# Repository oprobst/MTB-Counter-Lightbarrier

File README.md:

# Lichtschranke mit Unterbrechungszähler

Diese Implementierung wurde mit dem Hintergrund erstellt, auf einem Mountain-Bike Trail die Anzahl der Durchfahrten zu messen. Mit kleineren Anpassungen, kann diese Schaltung aber auch für alles Mögliche verwendet werden.

* Ziel ist es, die Unterbrechungen der Lichtschranke zu zählen. Dies wird über den gesamten Lebenszyklus, wie auch auf täglicher Basis gezählt.
* Weitere Anforderung ist ein möglichst geringer Stromverbrauch, um einen Einsatz mit Batterie im Feld zu vereinfachen.

# Bedienungsanleitung

An der rechten oberen Seite der Verteilerdose ist ein Magnetkontakt angebracht. Dieser kann genutzt werden, um das Display zu aktivieren. Sobald ein Magnet an das Gehäuse gehalten wird, aktiviert sich das Display für 5 Minuten. Im Normalbetrieb ist das Display aus, um Strom zu sparen und um zu verhindern, dass Fuchs und Hase daran herum spielen. Ein weiterer Vorteil des Magneten liegt darin, dass eine fehleranfällige Gehäusedurchführung für einen Taster eingespart werden kann.

## Display
Auf dem Display sind mehrere Zahlen abgebildet. Links oben ist die Gesamtzahl der aufgezeichneten Unterbrechungen. Diese Zahl wird mit jeder Durchfahrt um einen Zähler erhöht.

In der unteren Zeile sind die vergangenen Tage dokumentiert. Es wird immer dann eine neue Zählung begonnen, wenn der Helligkeitssensor einen Sonnenaufgang registriert oder wenn das System neu gestartet (oder resettet) wird.
Dabei steht jede Zahl für einen Tag. In dem unten abgebildeten Beispiel sind am heutigen Tag 15 Fahrten, gestern 0 und vorgestern 1 Unterbrechung gemessen worden. Der Speicher lässt nur 253 Zählungen zu, finden mehr Durchfahrten an einem Tag statt, so zeigt das Display 'MAX' an. Dies beeinflusst allerdings nicht die Zählung der gesamten Durchgänge oben links.

Um mehr als die letzten 4 Tage anzuzeigen, schaltet der Zähler mehrere Seiten durch. Dabei wird jede Seite wird für 5 Sekunden angezeigt. Im Beispiel befindet sich der Zähler noch auf Seite 0, visualisiert durch die Angabe 'P0'. Folglich wird in der Zeile unten auf erster Stelle der aktuelle Tag und im Weiteren die vergangenen drei Tage dargestellt.
Würde hier z.B. 'P3' stehen, so rechne man einfach die (Page)3 * 4(Tage) um auf den Tag des ersten Wertes in der Vergangenheit zu kommen. In diesem Fall würde man also die Durchfahrten von vor 12, vor 13, vor 14 und vor 15 Tagen angezeigt bekommen.

Letztlich steht ganz rechts oben eine Zahl mit einer Nachkommastelle. Hierbei handelt es sich um die aktuelle Batteriespannung. Sie muss im Regelfall zwischen 9V und 14V liegen. Liegt sie darunter, lädt die Solarzelle die Batterie nicht mehr. Liegt sie darüber, ist irgendetwas magisches passiert.

Der Kontrast des Displays lässt sich mit einer Stellschraube auf halber Höhe des Zählers einstellen.

## Zähler zurück setzen

Es ist möglich den Zähler auf 0 zurück zu setzen. Dafür muss der linke ('Debug') Knopf gedrückt und gehalten werden. Dann der rechte ('Reset' Knopf) kurz gedrückt werden, während der Debug Knopf für weitere 10 Sekunden gehalten werden muss. Das Display zählt einen Countdown herunter und meldet dann 'Speicher gelöscht'.

# Umsetzung

## Generelles Setup

Die Schaltung ist mit einer 10W Peak Solarzelle ausgestattet, die über einen Solarladeregler einen 5,4Ah Bleigelakku lädt. Diese versorgt die Schaltung über eine Sicherung (<=100mA ist ausreichend).
Aus der Versorgungsspannung wird die Lichtschranke direkt bedient und die Platine über einen 3,3V DC/DC Wandler betrieben.

Die reine Zählerschaltung (ohne den Batterie-Laderegler) benötigt - je nach Batteriespannung - etwa 4mA bei Tag und 0,7mA bei Nacht.

## Programmierung

Der Code ist nicht besonders schön und beruflich würde ich ihn dem Ersteller oder der Erstellerin um die Ohren hauen. Aber da ich das während eines Feierabend-Bierchens getippselt habe, setze ich mal andere Maßstäbe an.
Um die Programmierung einfach zu halten, werden die Arduino Libraries verwendet. Das ist nicht ganz durchgängig möglich, da die Pins für den Quarz als Input verwendet werden, was die Lib nicht vorsieht.

Wird die Lichtschranke unterbrochen, so findet für weitere 300ms keine weitere Messung mehr statt. Hierdurch wird verhindert, dass ein Arm und ein darauf folgender Oberkörper nicht als 2 Radfahrer erkannt werden.

Wird der Debug Knopf gedrückt und gehalten, so zeigt das Display den aktuell gemessenen Helligkeitswert (B:) an, sowie ein D für Day oder ein N für Night. Es folgt die Versorgungsspannungsmessung, sowie die Zählung des aktuellen Tages (C:) und die Dauer der letzten Unterbrechung (D:).

## Hardware
Als Microcontroller kommt der gute ATMega328P zum Einsatz. Um den Strombedarf gering zu halten, kommt der Zähler ohne externen Quarz und operiert auf lediglich 1 MHz per Fuses-Einstellung.
Dadurch liegt die maximale Auflösung bei 15ms. Grob über den Daumen gepeilt könnte es also sein, dass Radfahrer die mit mehr als 80 km/h auf dem Trail unterwegs sind nicht mehr erfasst werden.

Die aktuell erstellte Version wurde prototypisch auf einer Lochstreifenplatine erstellt. Spätere Versionen können bei erfolgreichem Dauertest auch auf professioneller gelayouteten Platinen umgesetzt werden.
Die momentane Implementierung speichert jeden Durchgang. Dadurch werden auch dann Zählungen gespeichert, wenn der Strom unerwartetet ausfällt. Nachteil ist die begrenzte Haltbarkeit des Speicherchips, der nur 100.000 Speichervorgänge garantiert.
Der Chip ist auf einen Sockel gesteckt und kann so einfach getauscht werden.

Generell sind die Widerstände eher großzügig zu Lasten den Genauigkeit dimensioniert mit dem Hintergedanken Strom zu sparen.

Die aktuelle Version arbeitet mit einem Hitatchi Display. Ich denke in den nächsten Versionen sollte ich dem Ganzen ein LCD Display spendieren, das ist irgendwie cooler und braucht auch nicht ganz so viele Datenleitungen. 

Als Phototransistor kommt der BP 103B-2 zum Einsatz. Für diesen Zweck nicht optimal, aber ich habe ihn mit einem sehr hohen Widerstand und einem Kondensator gebändigt. Dadurch ist die Messung sehr ungenau, aber um Hell und Dunkel zu unterscheiden reicht es.

Ein Verpolungsschutz wird durch eine Diode in Durchgangsrichtung realisiert. Auf die 0,7 Volt kommt es auch nicht mehr an. 

Zum Programmieren ist ein 6 poliger Standard Pinheader vorgesehen. Theoretisch muss man aufpassen, dass der Programmer mit 3,3V arbeitet, praktisch kann das Teil eine kurze Überspannung auf 5 V während des Programmierens ab.

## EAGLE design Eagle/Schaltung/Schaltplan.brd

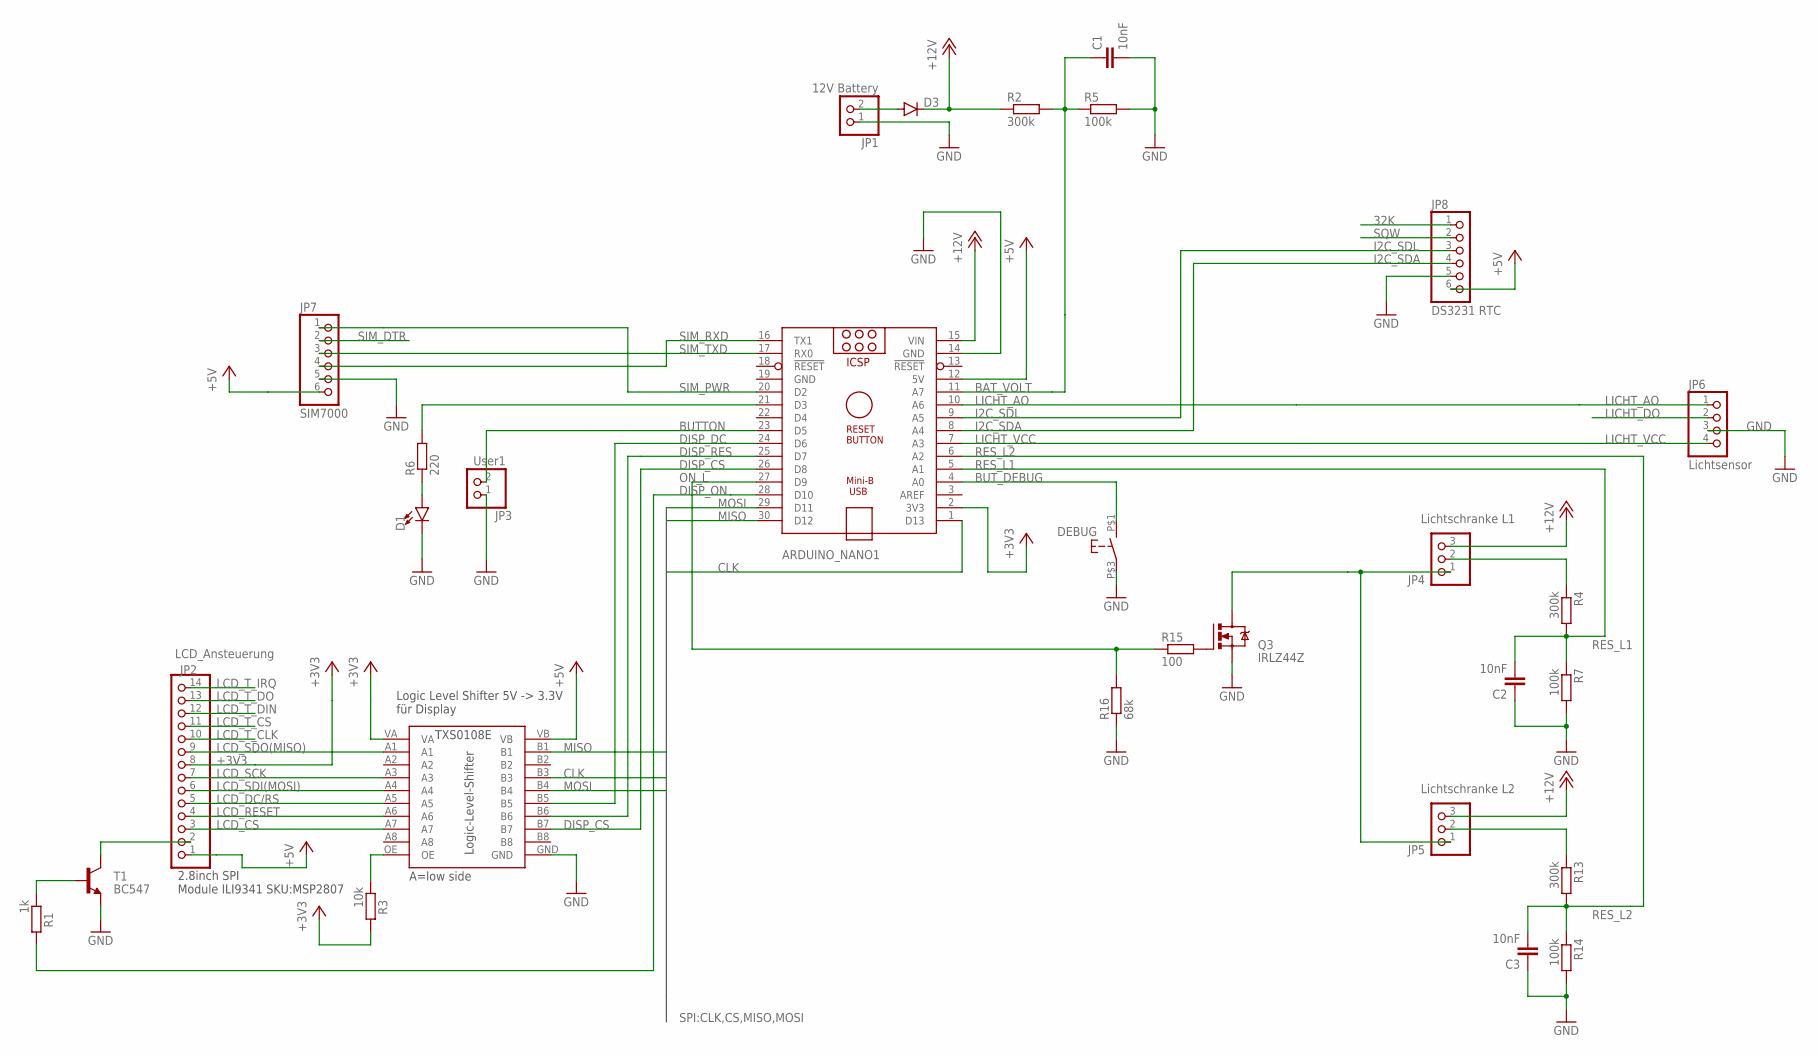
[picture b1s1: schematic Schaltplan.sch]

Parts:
ARDUINO_NANO1: ARDUINO_NANO
C1, C2, C3: 10nF; C0805K
D1: LED5MM; LED_5MM
D3: 1N4004; DO41-10
DEBUG: SCHLIESSER_TASTSCHALTER; B3F-10XX
JP1: 12V Battery; 1X02
JP2: LCD_Ansteuerung; 1X14
JP3: User1; 1X02
JP4: Lichtschranke L1; 1X03
JP5: Lichtschranke L2; 1X03
JP6: Lichtsensor; 1X04
JP7: SIM7000; 1X06
JP8: DS3231 RTC; 1X06
Q3: IRLZ44Z; TO220BH
R1: 1k; R1206
R2, R4, R13: 300k; R1206
R3: 10k; R1206
R5, R7, R14: 100k; R1206
R6: 220; R1206
R15: 100; R1206
R16: 68k; R1206
T1: BC547; TO92
U$2: TXS0108E_LOGIC_LEVEL_SHIFTER

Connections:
32K: JP8.1
+3V3: ARDUINO_NANO1.2 (3V3), JP2.8, R3.2, U$2.VA
+5V: ARDUINO_NANO1.12 (5V), JP2.1, JP7.6, JP8.6, U$2.VB
+12V: ARDUINO_NANO1.15 (VIN), D3.C, JP4.3, JP5.3, R2.1
BAT_VOLT: ARDUINO_NANO1.11 (A7), C1.1, R2.2, R5.1
BUTTON: ARDUINO_NANO1.23 (D5), JP3.2
BUT_DEBUG: ARDUINO_NANO1.4 (A0), DEBUG.P$1 (3)
CLK: ARDUINO_NANO1.1 (D13), U$2.B3
DISP_CS: ARDUINO_NANO1.26 (D8), U$2.B7
DISP_DC: ARDUINO_NANO1.24 (D6), U$2.B5
DISP_ON: ARDUINO_NANO1.28 (D10), R1.2
DISP_RES: ARDUINO_NANO1.25 (D7), U$2.B6
GND: ARDUINO_NANO1.14 (GND), ARDUINO_NANO1.19 (GND), C1.2, C2.1, C3.1, D1.K (C), DEBUG.P$3 (4), JP1.1, JP3.1, JP6.3, JP7.5, JP8.5, Q3.S, R5.2, R7.2, R14.2, R16.1, T1.1 (E), U$2.GND
I2C_SDA: ARDUINO_NANO1.8 (A4), JP8.4
I2C_SDL: ARDUINO_NANO1.9 (A5), JP8.3
LCD_CS: JP2.3, U$2.A7
LCD_DC/RS: JP2.5, U$2.A5
LCD_RESET: JP2.4, U$2.A6
LCD_SCK: JP2.7, U$2.A3
LCD_SDI(MOSI): JP2.6, U$2.A4
LCD_SDO(MISO): JP2.9, U$2.A1
LCD_T_CLK: JP2.10
LCD_T_CS: JP2.11
LCD_T_DIN: JP2.12
LCD_T_DO: JP2.13
LCD_T_IRQ: JP2.14
LICHT_AO: ARDUINO_NANO1.10 (A6), JP6.1
LICHT_DO: JP6.2
LICHT_VCC: ARDUINO_NANO1.7 (A3), JP6.4
MISO: ARDUINO_NANO1.30 (D12), U$2.B1
MOSI: ARDUINO_NANO1.29 (D11), U$2.B4
unnamed: JP5.2, R13.1
unnamed: D3.A, JP1.2
unnamed: JP2.2, T1.3 (C)
unnamed: ARDUINO_NANO1.21 (D3), R6.2
unnamed: JP4.1, JP5.1, Q3.D
unnamed: R1.1, T1.2 (B)
unnamed: D1.A, R6.1
unnamed: R3.1, U$2.OE
unnamed: Q3.G, R15.2
unnamed: JP4.2, R4.1
ON_L: ARDUINO_NANO1.27 (D9), R15.1, R16.2
RES_L1: ARDUINO_NANO1.5 (A1), C2.2, R4.2, R7.1
RES_L2: ARDUINO_NANO1.6 (A2), C3.2, R13.2, R14.1
SIM_DTR: JP7.2
SIM_PWR: ARDUINO_NANO1.20 (D2), JP7.1
SIM_RXD: ARDUINO_NANO1.16 (TX1), JP7.4
SIM_TXD: ARDUINO_NANO1.17 (RX0), JP7.3
SQW: JP8.2

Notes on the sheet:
A=low side
2.8inch SPI Module ILI9341 SKU:MSP2807
Logic Level Shifter 5V -> 3.3V für Display

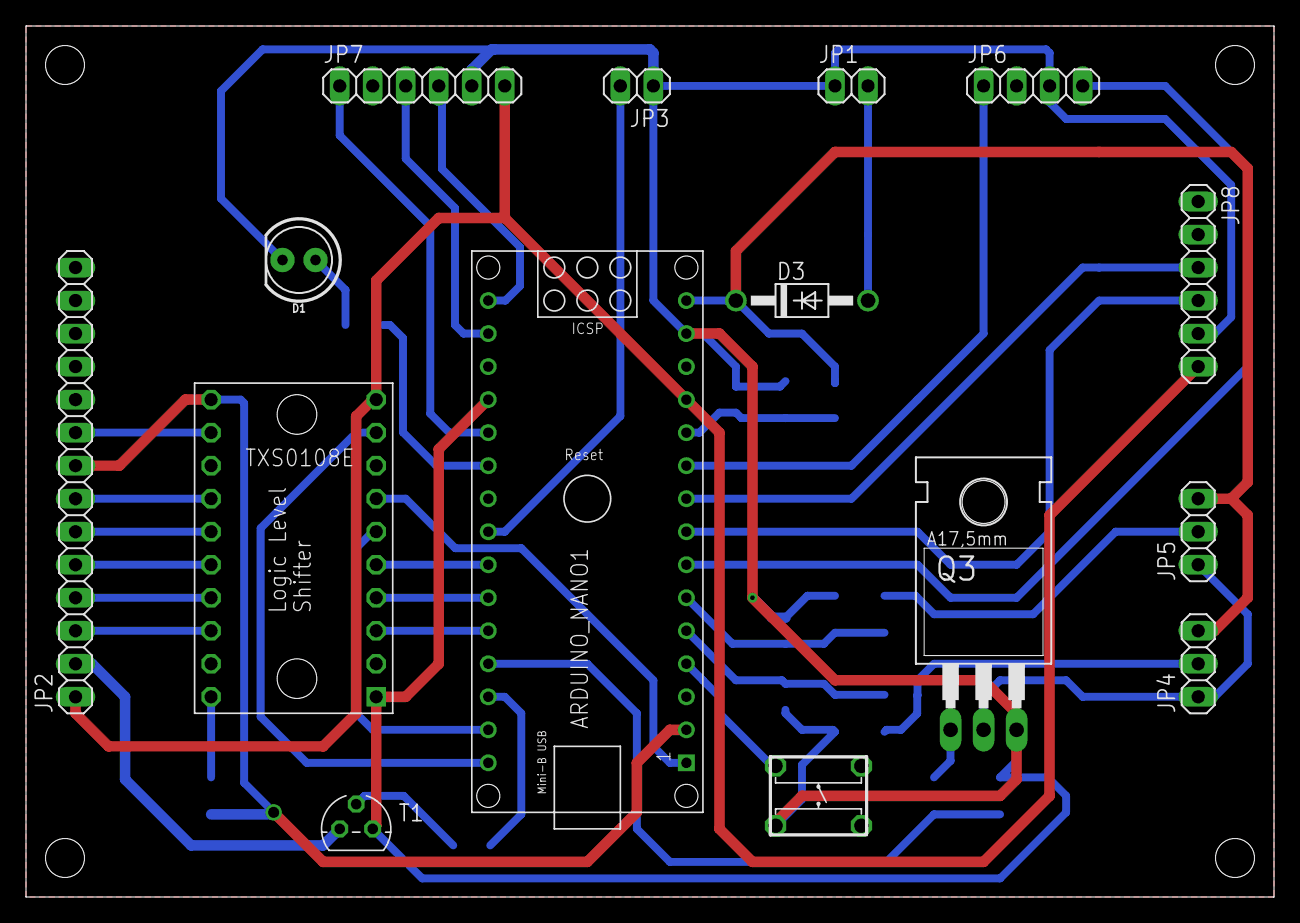
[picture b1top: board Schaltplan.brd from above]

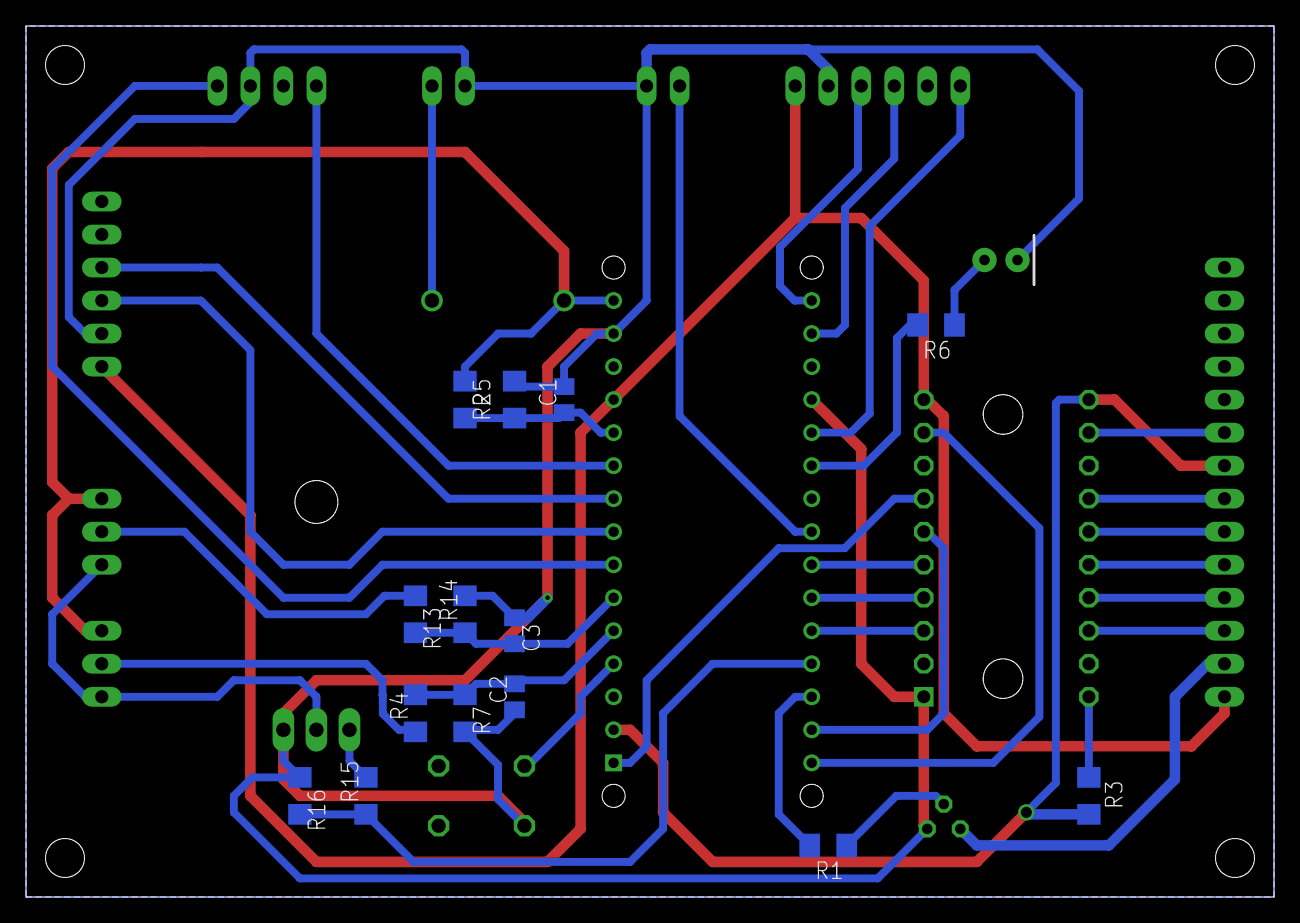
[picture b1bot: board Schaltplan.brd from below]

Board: 2 copper layers, 96.0 x 67.0 mm, 29 parts (14 on the bottom side), 40 nets.

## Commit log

2023-05-14 checkin to GIT
2023-05-14 Initial storing day counts
2023-05-19 Lot's of improvements...
2023-05-23 Bugfix for pwrdwn (int overflow)
2023-05-26 Described general setup
2023-05-31 Readme in German and extended
2023-05-31 Corrected comment about fuses
2023-05-31 Mainly typos
2023-05-31 typo
2025-05-18 Update auf 2 Lichtschranken
2025-05-18 gitignore erweitert
2025-06-02 Initial server implementation for counter
2025-06-03 circuit added
2025-06-03 Buggy State commited.

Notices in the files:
parts and their libraries:
SparkFun-LED: Licensing: Creative Commons ShareAlike 4.0 International - https://creativecommons.org/licenses/by-sa/4.0
